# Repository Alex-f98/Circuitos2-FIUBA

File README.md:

Los archivos de cursas son muy pesados para subir al github.

Solo se sube el TP final del mismo, dentro esta el informe.
Como fue un tp en donde se nos hacia seguimiento se pidio que el informe sea breve y presente solo resultados.

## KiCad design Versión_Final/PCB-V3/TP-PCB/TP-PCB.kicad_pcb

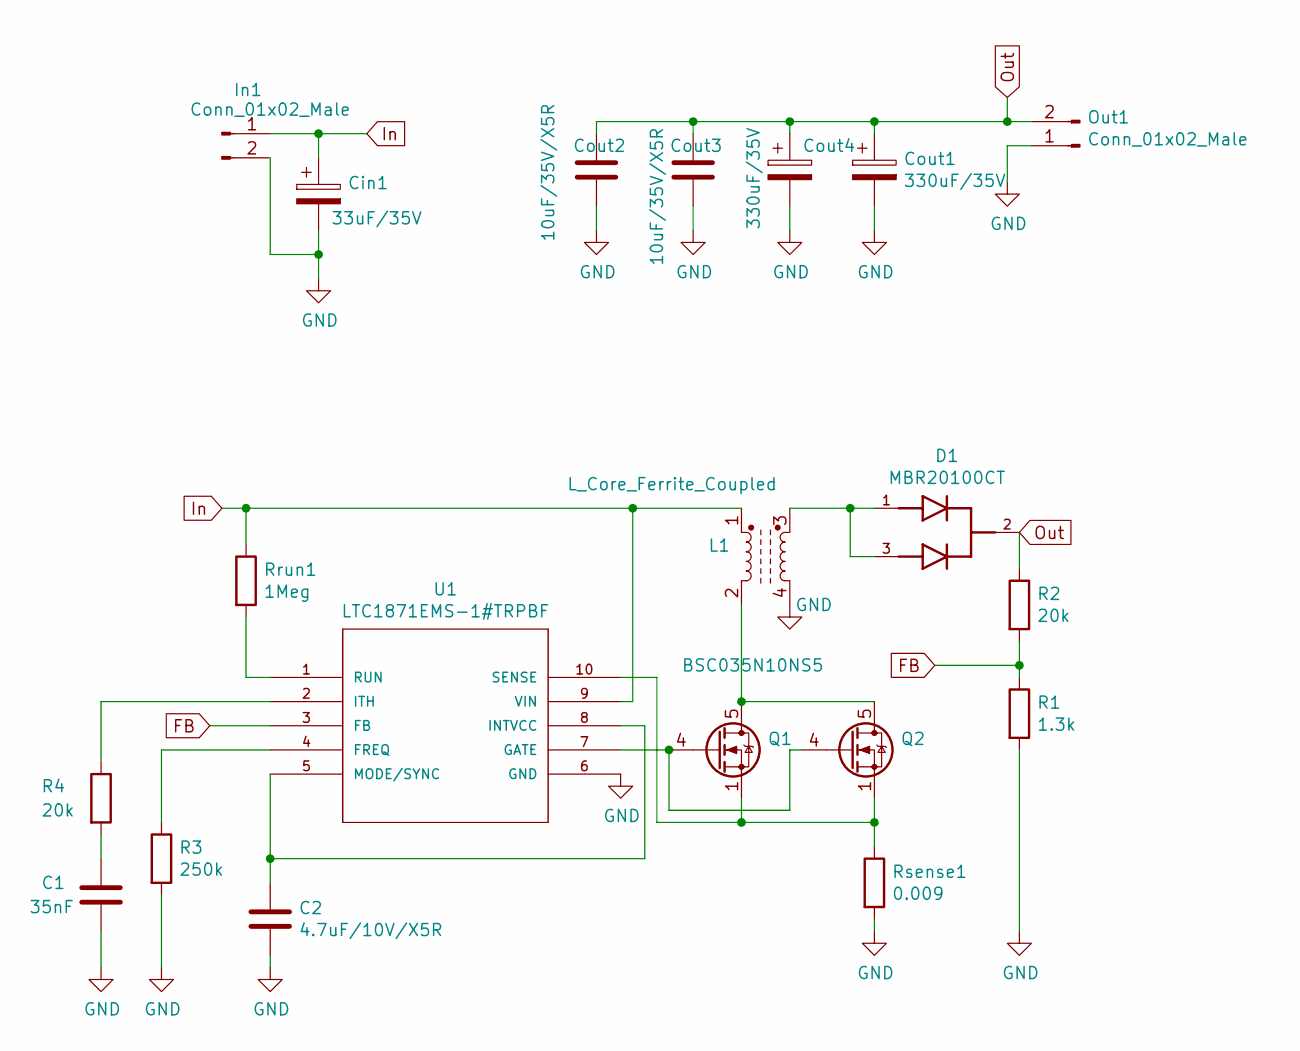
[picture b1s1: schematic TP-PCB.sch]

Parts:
C1: 35nF; CP_EIA-3216-18_Kemet-A
C2: 4.7uF/10V/X5R; CP_EIA-3216-18_Kemet-A
Cin1: 33uF/35V; CP_Elec_3x5.3
Cout1, Cout4: 330uF/35V; CP_Elec_3x5.3
Cout2, Cout3: 10uF/35V/X5R; CP_EIA-3216-18_Kemet-A
D1: MBR20100CT; TO254P1521X483-4N; PARTREV 8-2
In1: Conn_01x02_Male; PinHeader_1x02_P2.00mm_Vertical_SMD_Pin1Left
L1: L_Core_Ferrite_Coupled; ALT_Carrete_E42-21-20
Out1: Conn_01x02_Male; PinHeader_1x02_P2.00mm_Vertical_SMD_Pin1Left
Q1, Q2: BSC035N10NS5; TDSON-8-1
R1: 1.3k; R_1206_3216Metric
R2, R4: 20k; R_1206_3216Metric
R3: 250k; R_1206_3216Metric
Rrun1: 1Meg; R_1206_3216Metric
Rsense1: 0.009; R_1206_3216Metric
U1: LTC1871EMS-1#TRPBF; MSOP-10_MS; MANUFACTURER_PART_NUMBER ltc1871ems7

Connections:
FB: R1.1, R2.2, U1.3 (FB)
GND: C1.2, C2.2, Cin1.2, Cout1.2, Cout2.2, Cout3.2, Cout4.2, In1.2, L1.4, Out1.1, R1.2, R3.2, Rsense1.2, U1.6 (GND)
In: Cin1.1, In1.1, L1.1, Rrun1.1, U1.9 (VIN)
unnamed: C1.1, R4.2
unnamed: C2.1, U1.5 (MODE/SYNC), U1.8 (INTVCC)
unnamed: D1.1, D1.3, L1.3
unnamed: L1.2, Q1.5 (D), Q2.5 (D)
unnamed: Q1.1 (S), Q1.2 (S), Q1.3 (S), Q2.1 (S), Q2.2 (S), Q2.3 (S), Rsense1.1, U1.10 (SENSE)
unnamed: Q1.4 (G), Q2.4 (G), U1.7 (GATE)
unnamed: R3.1, U1.4 (FREQ)
unnamed: R4.1, U1.2 (ITH)
unnamed: Rrun1.2, U1.1 (RUN)
Out: Cout1.1, Cout2.1, Cout3.1, Cout4.1, D1.2, Out1.2, R2.1

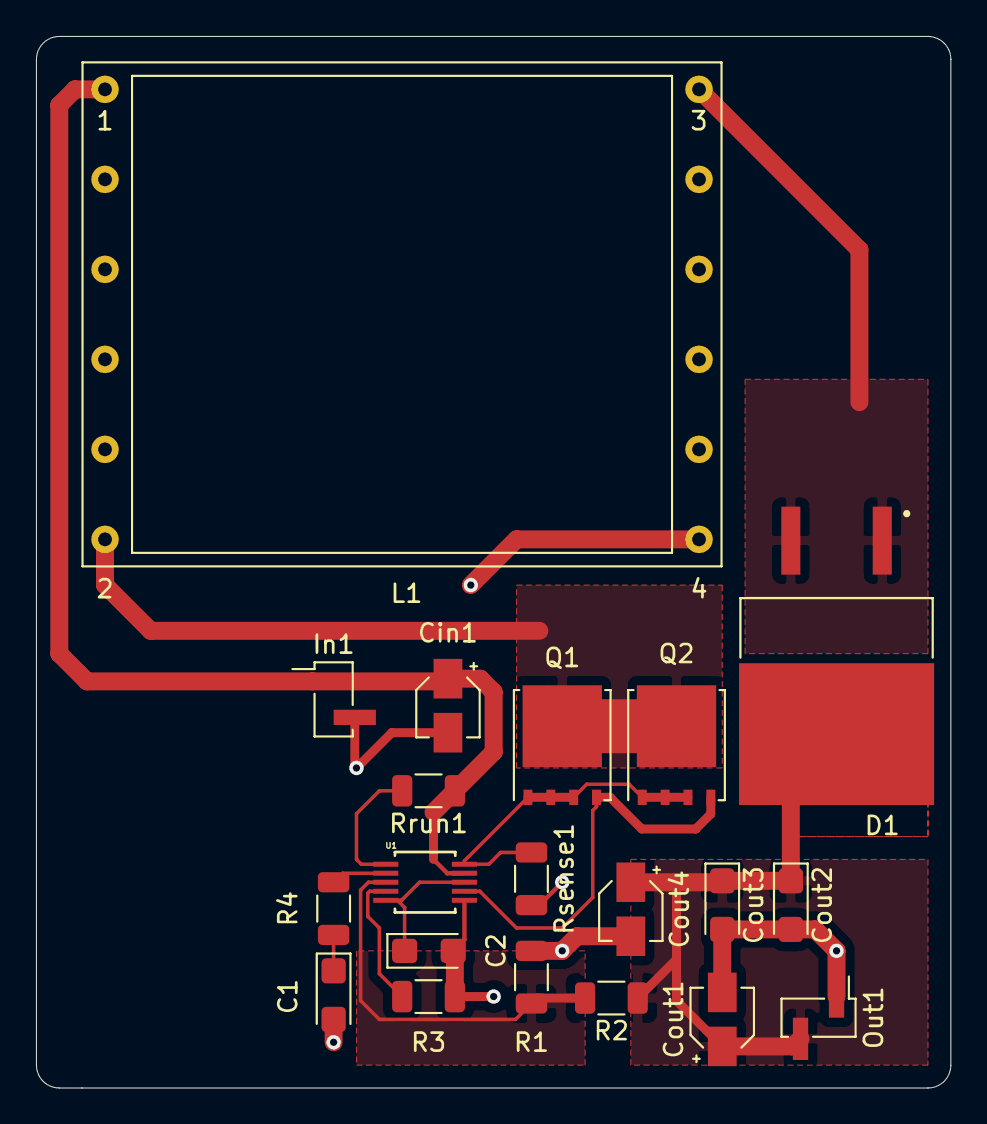
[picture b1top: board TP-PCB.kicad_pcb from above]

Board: 2 copper layers, 50.8 x 58.4 mm, 20 parts (0 on the bottom side), 13 nets.

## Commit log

2025-02-20 TP final circuitos2
